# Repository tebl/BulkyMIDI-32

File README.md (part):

# BulkyMIDI-32
When I was young I'd heard rumours about a fantastical sound card for the computer known as the Roland MT-32 - imagining that if it was good enough to be the default sound device for games such as Monkey Island, then it had to be good! Of course I was a kid at the time, the kind that didn't even have enough money to even be allowed inside the kind of stores that would sell this stuff. Fast forward to adulthood and I learned that it wasn't a sound card at all - it was a standalone MIDI-module! The second thing I learned was that they originally were, and still are, incredibly expensive items. Especially for those of us who were born without any sense of rhythm.

Cue other incredibly talented people found on the Internet, in particular for creating the [mt32-pi](https://github.com/dwhinham/mt32-pi) project - allowing people like myself to build a device capable of at least emulating one of these fantastical devices. All it takes is a somewhat cheap, mostly available Raspberry Pi 3 or 4. As with everything I enjoy playing around with, as long as it is simple enough for me to do so - I'll look into building my own version of it. Granted, I may have cheated more than a little bit by starting out with a copy of the design files for [clymsyMIDI](https://github.com/gmcn42/clumsyMIDI) as my starting point.

I had a lot of fun building the original *BulkyMIDI-32*, my process can best be described as an exciting journey down a rabbit hole of all things MIDI including similarly themed audio projects. This resulted in a multitude of adapters built for connecting things together, including a whole host of interesting modules that can be either used with the *BulkyMIDI-32* - or - in many cases they can be also be used by themselves or alongside other vintage music equipment. In order to keep things separate I've split the modules-section so that you'd quickly be able to determine which PCB designs could belong together.

- [1> Modules](#1-modules)
  - [1.1> BulkyMIDI-32](#11-bulkymidi-32)
  - [1.2> BulkyMIDI-32 Audio Switch](#12-bulkymidi-32-audio-switch)
  - [1.3> BulkyMIDI-32 Channel Monitor](#13-bulkymidi-32-channel-monitor)
  - [1.4> BulkyMIDI-32 Channel Monitor 2](#14-bulkymidi-32-channel-monitor-2)
  - [1.5> BulkyMIDI-32 Dexed](#15-bulkymidi-32-dexed)
  - [1.6> BulkyMIDI-32 ExModule](#16-bulkymidi-32-exmodule)
  - [1.7> BulkyMIDI-32 Input Switch](#17-bulkymidi-32-input-switch)
  - [1.8> BulkyMIDI-32 Internal](#18-bulkymidi-32-internal)
  - [1.9> BulkyMIDI-32 Play](#19-bulkymidi-32-play)
  - [1.10> BulkyMIDI-32 Power Switch](#110-bulkymidi-32-power-switch)
  - [1.11> BulkyMIDI-32 VU SIDi](#111-bulkymidi-32-vu-sidi)
- [2> Adapters](#2-adapters)
- [3> Documentation](#3-documentation)
- [4> Acknowledgements](#4-acknowledgements)

# 1> Modules
For the technical details as well as information regarding the modules included by this specific github project, consult the table below. Follow the [documentation](https://github.com/tebl/BulkyMIDI-32/tree/main/documentation) links for build instructions, BOM and anything else you'd need for that specific module. Faceplates and any backplates listed are for the most most part only decorative, allowing you to put together something similar to a case without actually requiring a 3d-printer. Also, check out the [schematics](https://github.com/tebl/BulkyMIDI-32/tree/main/documentation) for more information about the electronic side of things.

As previously mentioned several modules has been designed as part of the same project, these add different functionality and due to their identical form factor - they can all be stacked to build your very own MIDI-mountain! Though they bear the *BulkyMIDI-32* name, they can all be used independently of the main [BulkyMIDI-32](#11-bulkymidi-32)-module - they will communicate using standard MIDI. Should you want to, they should be able to live happily alongside your vintage MIDI-devices.

| Module                            | Description                                      |
| --------------------------------- | ------------------------------------------------ | 
| [BulkyMIDI-32](#11-bulkymidi-32)  | Main *BulkyMIDI-32*-module (running *mt32-pi*).
| [BulkyMIDI-32 Audio Switch](#12-bulkymidi-32-audio-switch) | Module for switching between various audio sources, similar to the source selection switch on a stereo system.
| [BulkyMIDI-32 Channel Monitor](#13-bulkymidi-32-channel-monitor) | MIDI-channel activity monitor, lights up an LED corresponding to the channel on activity. Implemented using basic CMOS logic chips.
| [BulkyMIDI-32 Channel Monitor 2](#14-bulkymidi-32-channel-monitor-2) | Mainly the same as above, except that the hardware is implemented using an *Arduino Pro Micro* and is therefore a lot easier to obtain the parts for.
| [BulkyMIDI-32 Dexed](#15-bulkymidi-32-dexed) | A variant of *BulkyMIDI-32* that was intended for running [MiniDexed](https://github.com/probonopd/MiniDexed).
| [BulkyMIDI-32 ExModule](#16-bulkymidi-32-exmodule) | *BulkyMIDI-32*-styled module for connecting modern WaveTable-modules up to MIDI-devices.
| [BulkyMIDI-32 Input Switch](#16-bulkymidi-32-input-switch) | Module for switching between up to four MIDI sources, the selected input is then replicated to three different THRU-ports. This allows you to easily switch between equipment as well as chain together different systems.
| [BulkyMIDI-32 Internal](#18-bulkymidi-32-internal) | *BulkyMIDI-32* built for installing in a 3.5" PC drivebay.
| [BulkyMIDI-32 Play](#19-bulkymidi-32-play) | Used for playing MIDI-files (*.MID*) from an SD-card using an *Arduino Pro Micro*. The hardware can also be uses as a basis for building a custom MIDI-merger, MIDI-message filtering or simply as a *USB to MIDI*-adapter.
| [BulkyMIDI-32 Power Switch](#110-bulkymidi-32-power-switch) | *BulkyMIDI-32*-module for managing power to other *BulkyMIDI-32*-modules.
| [BulkyMIDI-32 VU SIDi](#111-bulkymidi-32-vu-sidi) | At the moment this is an LM3915-based VU-meter.

## 1.1> BulkyMIDI-32

**Status:** Completed

This is the main attraction of this entire repository. If you came here looking to build an awesome looking mt32-pi, then this is at least one of them. You're given the option of picking the cheaper route by only building up a basic module, that's the main PCB and nothing else. Alternatively, and this is the part that makes it awesome, you can build the whole thing as shown above. Given the really low cost of PCB fabrication on this side of the widely advertised oncoming apocalypse, I recommend that you build a complete unit. The list below will include alternate versions of some boards, so you need to decide which of them you want or need based on their description.

| Module                 | Required    | Description                        | Documentation                      | Order      |
| ---------------------- | ----------- | ---------------------------------- | ---------------------------------- | ---------- |
| [BulkyMIDI-32](https://github.com/tebl/BulkyMIDI-32/tree/main/BulkyMIDI-32%20Module) | Yes | Main module | [Documentation](https://github.com/tebl/BulkyMIDI-32/tree/main/BulkyMIDI-32%20Module), [BOM](https://github.com/tebl/BulkyMIDI-32/blob/main/BulkyMIDI-32%20Module/README.md#3-bom), [Setting it up](https://github.com/tebl/BulkyMIDI-32/blob/main/documentation/setting_it_up.md), [Getting started](https://github.com/tebl/BulkyMIDI-32/blob/main/documentation/getting_started.md) | [PCBWay](https://www.pcbway.com/project/shareproject/BulkyMIDI_32_35d2ed18.html)
| [BulkyMIDI-32 Panel](https://github.com/tebl/BulkyMIDI-32/tree/main/BulkyMIDI-32%20Module%20Panel) | Recommended | Adds a vertical surface for mounting switches and rotary encoder. | [Documentation](https://github.com/tebl/BulkyMIDI-32/tree/main/BulkyMIDI-32%20Module%20Panel), [BOM](https://github.com/tebl/BulkyMIDI-32/tree/main/BulkyMIDI-32%20Module%20Panel/README.md#3-bom) | [PCBWay](https://www.pcbway.com/project/shareproject/BulkyMIDI_32_Module_Panel_17b7fa7c.html)
| [BulkyMIDI-32 Front panel (FP1)](https://github.com/tebl/BulkyMIDI-32/tree/main/faceplates/BulkyMIDI-32%20Module%20FP1) | Optional | Decorative front panel, mounts on [BulkyMIDI-32 Panel](https://github.com/tebl/BulkyMIDI-32/tree/main/BulkyMIDI-32%20Module%20Panel). Designed for use with [BulkyMIDI-32 Extras](https://github.com/tebl/BulkyMIDI-32/tree/main/BulkyMIDI-32%20Extras). | [Documentation](https://github.com/tebl/BulkyMIDI-32/tree/main/faceplates/BulkyMIDI-32%20Module%20FP1) | [PCBWay](https://www.pcbway.com/project/shareproject/BulkyMIDI_32_Module_Faceplate_FP1_92a2878f.html)
| [BulkyMIDI-32 Front panel (FP2)](https://github.com/tebl/BulkyMIDI-32/tree/main/faceplates/BulkyMIDI-32%20Module%20FP2) | Recommended | Decorative front panel, mounts on [BulkyMIDI-32 Panel](https://github.com/tebl/BulkyMIDI-32/tree/main/BulkyMIDI-32%20Module%20Panel) | [Documentation](https://github.com/tebl/BulkyMIDI-32/tree/main/faceplates/BulkyMIDI-32%20Module%20FP2) | [PCBWay](https://www.pcbway.com/project/shareproject/BulkyMIDI_32_Module_Faceplate_FP2_946cc4c8.html)
| [BulkyMIDI-32 Extras](https://github.com/tebl/BulkyMIDI-32/tree/main/BulkyMIDI-32%20Extras) | Optional | Adds passive audio mixing, RS-232 connectivity and RS-232 baud rate translation. | [Documentation](https://github.com/tebl/BulkyMIDI-32/tree/main/BulkyMIDI-32%20Extras), [BOM](https://github.com/tebl/BulkyMIDI-32/tree/main/BulkyMIDI-32%20Extras/README.md#3-bom) | [PCBWay](https://www.pcbway.com/project/shareproject/BulkyMIDI_32_Extras_9be44f98.html)
| [BulkyMIDI-32 Faceplate (FB2)](https://github.com/tebl/BulkyMIDI-32/tree/main/faceplates/BulkyMIDI-32%20FB2) | Optional | Faceplate that goes on top of the device | [Documentation](https://github.com/tebl/BulkyMIDI-32/tree/main/faceplates/BulkyMIDI-32%20FB2) | [PCBWay](https://www.pcbway.com/project/shareproject/BulkyMIDI_32_Faceplate_FB2_c07272e8.html)

## 1.2> BulkyMIDI-32 Audio Switch

**Status:** Completed

One of the drawbacks to using a vintage boombox as my main stereo speaker system in my workshop, is that only has a single audio input - meaning that I would normally have to switch around cables all the time. Ordinarily I shouldn't complain as much about that, as not everyone is lucky enough to have an input - at all! This doesn't solve the problem of not having any, but you do get the option of turning a single input into as many as you'd like with this Audio Switch. If you need more than six, build more than one!

To select the one you want, just push a button and almost instantly you'll hear an exciting click from the corresponding relay. Did I need a relay for this? Probably not. I just like using relays from time to time.

| Module                 | Required    | Description                        | Documentation                      | Order      |
| ---------------------- | ----------- | ---------------------------------- | ---------------------------------- | ---------- |
| [Audio Switch](https://github.com/tebl/BulkyMIDI-32/tree/main/BulkyMIDI-32%20Audio%20Switch) | Yes | Main module | [Documentation](https://github.com/tebl/BulkyMIDI-32/tree/main/BulkyMIDI-32%20Audio%20Switch), [BOM](https://github.com/tebl/BulkyMIDI-32/blob/main/BulkyMIDI-32%20Audio%20Switch/README.md#3-bom) | [PCBWay](https://www.pcbway.com/project/shareproject/BulkyMIDI_32_Audio_Switch_118316c8.html)
| [Audio Switch Panel](https://github.com/tebl/BulkyMIDI-32/tree/main/BulkyMIDI-32%20Audio%20Switch%20Panel) | Optional | Adds a vertical surface installing switches as well as adding channel indicator LEDs. | [Documentation](https://github.com/tebl/BulkyMIDI-32/tree/main/BulkyMIDI-32%20Audio%20Switch%20Panel), [BOM](https://github.com/tebl/BulkyMIDI-32/blob/main/BulkyMIDI-32%20Audio%20Switch%20Panel/README.md#3-bom) | [PCBWay](https://www.pcbway.com/project/shareproject/BulkyMIDI_32_Audio_Switch_Panel_a10b5ecb.html)
| [Audio Switch Front Panel (FP1)](https://github.com/tebl/BulkyMIDI-32/tree/main/faceplates/BulkyMIDI-32%20Audio%20Switch%20FP1) | Optional | Decorative front panel, mounts on [Audio Switch Panel](https://github.com/tebl/BulkyMIDI-32/tree/main/BulkyMIDI-32%20Audio%20Switch%20Panel). | [Documentation](https://github.com/tebl/BulkyMIDI-32/tree/main/faceplates/BulkyMIDI-32%20Audio%20Switch%20FP1) | [PCBWay](https://www.pcbway.com/project/shareproject/BulkyMIDI_32_Audio_Switch_Faceplate_FP1_fc2b542a.html)
| [BulkyMIDI-32 Faceplate (FB2)](https://github.com/tebl/BulkyMIDI-32/tree/main/faceplates/BulkyMIDI-32%20FB2) | Optional | Faceplate that goes on top of the device | [Documentation](https://github.com/tebl/BulkyMIDI-32/tree/main/faceplates/BulkyMIDI-32%20FB2) | [PCBWay](https://www.pcbway.com/project/shareproject/BulkyMIDI_32_Faceplate_FB2_c07272e8.html)

## 1.3> BulkyMIDI-32 Channel Monitor

**Status:** Working, but documentation is missing.

One of the first things I wanted to add to the *BulkyMIDI-32* was more blinking lights, as it turns out there were devices back in the day that did this - the were called channel monitors. Their purpose is simply to have an LED for each of the 16 MIDI channels, then as a MIDI-message passes through that contains channel information - the corresponding LED is lit up and will stay on for some time.

The circuit design was based on an article by W. Dunczewski, titled *MIDI Channel Monitor* and was printed in the 1993 october issue of Elektor Electronics. Besides the obvious attraction to blinking lights in controlled forms, what I liked about it is that everything is implemented entirely in basic CMOS logic chips (there's no traditional CPU or MCU handling the data).

| Module                 | Required    | Description                        | Documentation                      | Order      |
| ---------------------- | ----------- | ---------------------------------- | ---------------------------------- | ---------- |
| [Channel Monitor](https://github.com/tebl/BulkyMIDI-32/tree/main/BulkyMIDI-32%20Channel) | Yes | Main module | [Documentation](https://github.com/tebl/BulkyMIDI-32/tree/main/BulkyMIDI-32%20Channel), [BOM](https://github.com/tebl/BulkyMIDI-32/blob/main/BulkyMIDI-32%20Channel/README.md#3-bom) | PCBWay
| [Channel Monitor Panel](https://github.com/tebl/BulkyMIDI-32/tree/main/BulkyMIDI-32%20Channel%20Panel) | Optional | Adds a vertical surface for mounting the 16 channel LEDs. | [Documentation](https://github.com/tebl/BulkyMIDI-32/tree/main/BulkyMIDI-32%20Channel%20Panel), [BOM](https://github.com/tebl/BulkyMIDI-32/blob/main/BulkyMIDI-32%20Channel20Panel/README.md#3-bom) | PCBWay
| [Channel Monitor Front Panel (FP1)](https://github.com/tebl/BulkyMIDI-32/tree/main/faceplates/BulkyMIDI-32%20Channel%20FP1) | Optional | Decorative front panel, mounts on [Channel Monitor Panel](https://github.com/tebl/BulkyMIDI-32/tree/main/BulkyMIDI-32%20Channel%20Panel). | [Documentation](https://github.com/tebl/BulkyMIDI-32/tree/main/faceplates/BulkyMIDI-32%20Channel%20FP1) | PCBWay
| [BulkyMIDI-32 Faceplate (FB2)](https://github.com/tebl/BulkyMIDI-32/tree/main/faceplates/BulkyMIDI-32%20FB2) | Optional | Faceplate that goes on top of the device | [Documentation](https://github.com/tebl/BulkyMIDI-32/tree/main/faceplates/BulkyMIDI-32%20FB2) | [PCBWay](https://www.pcbway.com/project/shareproject/BulkyMIDI_32_Faceplate_FB2_c07272e8.html)

## 1.4> BulkyMIDI-32 Channel Monitor 2

**Status:** Working, but documentation is missing.

This module displays MIDI-channel activity in realtime, with an LED for each of the 16 channels. While it effectively does the same as the [BulkyMIDI-32 Channel Monitor](#13-bulkymidi-32-channel-monitor), I also wanted to build a version that could be put together using parts that aren't quite as *vintage* as the parts required by that module.

In the end, the core of the module was implemented using an Arduino Pro Micro in combination with a couple of shift registers. In theory the board can be built up as a simple *USB-to-MIDI* converter, or it can be used to have the MCU process MIDI-messages - note that Arduino *sketches* to do any of this do not exist. 

| Module                 | Required    | Description                        | Documentation                      | Order      |
| ---------------------- | ----------- | ---------------------------------- | ---------------------------------- | ---------- |
| [Channel Monitor 2](https://github.com/tebl/BulkyMIDI-32/tree/main/BulkyMIDI-32%20Channel%202) | Yes | Main module | [Documentation](https://github.com/tebl/BulkyMIDI-32/tree/main/BulkyMIDI-32%20Channel%202), [BOM](https://github.com/tebl/BulkyMIDI-32/blob/main/BulkyMIDI-32%20Channel%202/README.md#3-bom) | PCBWay
| [Channel Monitor Panel](https://github.com/tebl/BulkyMIDI-32/tree/main/BulkyMIDI-32%20Channel%20Panel) | Optional | Adds a vertical surface for mounting the 16 channel LEDs. | [Documentation](https://github.com/tebl/BulkyMIDI-32/tree/main/BulkyMIDI-32%20Channel%20Panel), [BOM](https://github.com/tebl/BulkyMIDI-32/blob/main/BulkyMIDI-32%20Channel20Panel/README.md#3-bom) | PCBWay
| [Channel Monitor Front Panel (FP1)](https://github.com/tebl/BulkyMIDI-32/tree/main/faceplates/BulkyMIDI-32%20Channel%20FP1) | Optional | Decorative front panel, mounts on [Channel Monitor Panel](https://github.com/tebl/BulkyMIDI-32/tree/main/BulkyMIDI-32%20Channel%20Panel). | [Documentation](https://github.com/tebl/BulkyMIDI-32/tree/main/faceplates/BulkyMIDI-32%20Channel%20FP1) | PCBWay
| [BulkyMIDI-32 Faceplate (FB2)](https://github.com/tebl/BulkyMIDI-32/tree/main/faceplates/BulkyMIDI-32%20FB2) | Optional | Faceplate that goes on top of the device | [Documentation](https://github.com/tebl/BulkyMIDI-32/tree/main/faceplates/BulkyMIDI-32%20FB2) | [PCBWay](https://www.pcbway.com/project/shareproject/BulkyMIDI_32_Faceplate_FB2_c07272e8.html)

## 1.5> BulkyMIDI-32 Dexed

**Status:** Untested prototype

A variant of *BulkyMIDI-32* that was intended for running [MiniDexed](https://github.com/probonopd/MiniDexed), a software that is similar to *MT32-PI* - except that it instead emulates up to eight Yamaha DX7 synthesizers on mostly the same hardware. I built one up and played around with it, my conclusion afterwards is that while it *may* work - I have absolutely no idea of how to use it. Or even a real keyboard for that matter. So in case someone finds it interesting enough to build one up using the files provided, please tell me whether it actually works. 

## 1.6> BulkyMIDI-32 ExModule

**Status:** Completed

There was a time when PC soundcards, mostly ISA, came with a *WaveTable*-header for attaching *WaveTable*-modules directly onto it it. Originally devised for mounting a separate *WaveBlaster*-module onto a *Creative Soundblaster 16*, but most often they're just referred to as *WaveTable*-headers as the form factor was inevitably adopted by several other companies who made similar modules with their own chipsets on it.

Ordering a selection of more modern modules from [serdashop.com](https://www.serdashop.com/) for installing into one of my vintage PCs, I couldn't decide on which one to put where - until I finally decided and realized that my AWE32 doesn't even have that feature. So for a year or so they've lived in the box the came in, buy in the end I figured it was time to do something with them. So I started building something to use them externally instead - following the guide up on [atari.joska.no](https://atari.joska.no/db50xg/), itself referencing an article printed in Elektor Electronics (july/august 1997), I ended up with the *BulkyMIDI-32 ExModule*. Plug a MIDI-cable into it, hook the audio output up to your amplifier and enjoy!

| Module                 | Required    | Description                        | Documentation                      | Order      |
| ---------------------- | ----------- | ---------------------------------- | ---------------------------------- | ---------- |
| [ExModule](https://github.com/tebl/BulkyMIDI-32/tree/main/BulkyMIDI-32%20ExModule) | Yes | Main module | [Documentation](https://github.com/tebl/BulkyMIDI-32/tree/main/BulkyMIDI-32%20ExModule), [BOM](https://github.com/tebl/BulkyMIDI-32/blob/main/BulkyMIDI-32%20ExModule/README.md#3-bom) | [PCBWay](https://www.pcbway.com/project/shareproject/BulkyMIDI_32_ExModule_6564c365.html)
| [ExModule Panel](https://github.com/tebl/BulkyMIDI-32/tree/main/BulkyMIDI-32%20ExModule%20Panel) | Optional | Adds a vertical surface installing switches as well as adding channel indicator LEDs. | [Documentation](https://github.com/tebl/BulkyMIDI-32/tree/main/BulkyMIDI-32%20ExModule%20Panel), [BOM](https://github.com/tebl/BulkyMIDI-32/blob/main/BulkyMIDI-32%20ExModule%20Panel/README.md#3-bom) | [PCBWay](https://www.pcbway.com/project/shareproject/BulkyMIDI_32_ExModule_Panel_8050038f.html)
| [ExModule Front Panel (FP1)](https://github.com/tebl/BulkyMIDI-32/tree/main/faceplates/BulkyMIDI-32%20ExModule%20FP1) | Optional | Decorative front panel, mounts on [ExModule Panel](https://github.com/tebl/BulkyMIDI-32/tree/main/BulkyMIDI-32%20ExModule%20Panel). | [Documentation](https://github.com/tebl/BulkyMIDI-32/tree/main/faceplates/BulkyMIDI-32%20ExModule%20FP1) | [PCBWay](https://www.pcbway.com/project/shareproject/BulkyMIDI_32_ExModule_Faceplate_FP1_640ef0bc.html)
| [BulkyMIDI-32 Faceplate (FB2)](https://github.com/tebl/BulkyMIDI-32/tree/main/faceplates/BulkyMIDI-32%20FB2) | Optional | Faceplate that goes on top of the device | [Documentation](https://github.com/tebl/BulkyMIDI-32/tree/main/faceplates/BulkyMIDI-32%20FB2) | [PCBWay](https://www.pcbway.com/project/shareproject/BulkyMIDI_32_Faceplate_FB2_c07272e8.html)

## 1.7> BulkyMIDI-32 Input Switch

**Status:** Completed

This module was created in order to easily switch between different MIDI inputs, the selected input is then replicated to three different THRU-ports. What this allows me to do on the input-side is to select between a keyboard, a USB MIDI-interfaces connected to a modern system and that of a  vintage computer system. Duplicating the MIDI-messages on different THRU-ports allow me to send the same data to several MIDI-devices, such as an original *Roland MT-32* as well as a *MT32-PI* (such as the BulkyMIDI-32 itself). 

| Module                 | Required    | Description                        | Documentation                      | Order      |
| ---------------------- | ----------- | ---------------------------------- | ---------------------------------- | ---------- |
| [Input Switch](https://github.com/tebl/BulkyMIDI-32/tree/main/BulkyMIDI-32%20Input%20Switch) | Yes | Main module | [Documentation](https://github.com/tebl/BulkyMIDI-32/tree/main/BulkyMIDI-32%20Audio%20Switch), [BOM](https://github.com/tebl/BulkyMIDI-32/blob/main/BulkyMIDI-32%20Audio%20Switch/README.md#3-bom) | PCBWay
| [Input Switch Panel](https://github.com/tebl/BulkyMIDI-32/tree/main/BulkyMIDI-32%20Input%20Switch%20Panel) | Optional | Adds a vertical surface installing switches as well as adding indicator LEDs. | [Documentation](https://github.com/tebl/BulkyMIDI-32/tree/main/BulkyMIDI-32%20Input%20Switch%20Panel), [BOM](https://github.com/tebl/BulkyMIDI-32/blob/main/BulkyMIDI-32%20Input%20Switch%20Panel/README.md#3-bom) | PCBWay
| [Input Switch Front Panel (FP1)](https://github.com/tebl/BulkyMIDI-32/tree/main/faceplates/BulkyMIDI-32%20Input%20Switch%20FP1) | Optional | Decorative front panel, mounts on [Input Switch Panel](https://github.com/tebl/BulkyMIDI-32/tree/main/BulkyMIDI-32%20Input%20Switch%20Panel). | [Documentation](https://github.com/tebl/BulkyMIDI-32/tree/main/faceplates/BulkyMIDI-32%20Input%20Switch%20FP1) | PCBWay
| [Input Switch Faceplate (FB2)](https://github.com/tebl/BulkyMIDI-32/tree/main/faceplates/BulkyMIDI-32%20Input%20Switch%20FB2) | Optional | Faceplate that goes on top of the device, similar to the two below - except it's missing a hole. | [Documentation](https://github.com/tebl/BulkyMIDI-32/tree/main/faceplates/BulkyMIDI-32%20Input%20Switch%20FB2) | PCBWay
| [BulkyMIDI-32 Faceplate (FB2)](https://github.com/tebl/BulkyMIDI-32/tree/main/faceplates/BulkyMIDI-32%20FB2) | Optional | Faceplate that goes on top of the device | [Documentation](https://github.com/tebl/BulkyMIDI-32/tree/main/faceplates/BulkyMIDI-32%20FB2) | [PCBWay](https://www.pcbway.com/project/shareproject/BulkyMIDI_32_Faceplate_FB2_c07272e8.html)

## 1.8> BulkyMIDI-32 Internal

**Status:** Working prototype

In many ways this is the module that this whole thing has been building towards, a 3.5" drive bay expansion for vintage PCs. Might fit into more equipment than this, but mainly just the blocky beige thing that you remember from your childhood (usually next to a CRT). Is this a sane thing to build without any kind of working 3d-printer available? No, it probably isn't. Did I build it anyway? Yes, and you're looking at the only finished version of it. Is it actually finished? No. Probably needs a bit of tweaking and the documentation to go with it.

## 1.9> BulkyMIDI-32 Play

**Status:** Completed

In many ways the missing module when it comes to playing around with a Roland MT-32, both the vintage kind as well as the emulated version that is the main *BulkyMIDI-32* module (running *mt32-pi*) - simply playing back a *.MID*-file without a computer attached to it. Implemented with an Arduino Pro Micro at its heart, you can put your files on an SD-card and play them back - use a long press when starting playback to loop the file, another long press to stop playback. During playback the rotary encoder encoder can be used to speed up or slow down the tempo.

Given that the designs have provisions for more than the expected number of MIDI-ports, a change in firmware can allow the hardware design to be used for entirely different purposes such as MIDI-message filtering, merging inputs and similar functionality.  

| Module                 | Required    | Description                        | Documentation                      | Order      |
| ---------------------- | ----------- | ---------------------------------- | ---------------------------------- | ---------- |
| [Play](https://github.com/tebl/BulkyMIDI-32/tree/main/BulkyMIDI-32%20Play) | Yes | Main module | [Documentation](https://github.com/tebl/BulkyMIDI-32/tree/main/BulkyMIDI-32%20Play), [BOM](https://github.com/tebl/BulkyMIDI-32/blob/main/BulkyMIDI-32%20Play/README.md#3-bom) | PCBWay
| [Play Panel](https://github.com/tebl/BulkyMIDI-32/tree/main/BulkyMIDI-32%20Play%20Panel) | Optional | Adds a vertical surface for oled-display and rotary encoder. | [Documentation](https://github.com/tebl/BulkyMIDI-32/tree/main/BulkyMIDI-32%20Play%20Panel), [BOM](https://github.com/tebl/BulkyMIDI-32/tree/main/BulkyMIDI-32%20Play%20Panel/README.md#3-bom) | PCBWay
| [Play Front Panel (FP1)](https://github.com/tebl/BulkyMIDI-32/tree/main/faceplates/BulkyMIDI-32%20Play%20FP1) | Optional | Decorative front panel, mounts on [Play Panel](https://github.com/tebl/BulkyMIDI-32/tree/main/BulkyMIDI-32%20Play%20Panel). | [Documentation](https://github.com/tebl/BulkyMIDI-32/tree/main/faceplates/BulkyMIDI-32%20Play%20FP1) | PCBWay
| [BulkyMIDI-32 Faceplate (FB2)](https://github.com/tebl/BulkyMIDI-32/tree/main/faceplates/BulkyMIDI-32%20FB2) | Optional | Faceplate that goes on top of the device | [Documentation](https://github.com/tebl/BulkyMIDI-32/tree/main/faceplates/BulkyMIDI-32%20FB2) | [PCBWay](https://www.pcbway.com/project/shareproject/BulkyMIDI_32_Faceplate_FB2_c07272e8.html)

## 1.10> BulkyMIDI-32 Power Switch
**Status:** Working, but last revision has not been tested.

Looking at this repository and the various devices contained within it, you'll soon get the impression that no man could possibly own that many 5v power supplies with that exact barrel plug already on it (2.1mm x 5.5mm barrel connector). I don't. I own exactly two, so that's one for the main BulkyMIDI-32 and one for everything else. So I got the idea that I would make something like the Audio Switch or Input Switch, except with power! And because I wanted a push to turn on, but really wanted a hold to turn off - I added an Arduino to the board. And some more relays. Because relays are cool, and a lot easier to understand for someone like me. You feed it power, then the other power connectors are hooked up to your other devices. In order to do so, you use a cable with a male plug on both ends (AliExpress has them listed as *DC male to male CCTV adapter connector cords*).

The design has provisions for using the first channel as a source for power, possibly with a different polarity. This is done by opting not to install the corresponding relay for the first channel, and changing out some of the wire links. Only reason I'm mentioning it in the first place is that music equipment traditionally use the same type of plug, but at a completely different voltage and polarity from what all of my *BulkyMIDI-32*-modules work with. If you mess up your cabling at some point, then there should be expectations of of smoke and tears, but it's nice to know that it's there as an option. If you know what you're doing.

## 1.11> BulkyMIDI-32 VU SIDi

**Status:** Prototype, with issues to work out

This is a module that I'll probably have to rethink properly, mostly because of attempting to integrate a little too much in one go without a proper understanding of either of them. The first part of it is a VU-meter based on the LM3915 chip which isn't a solution I particularly enjoyed using, at least in part due to one of the two modes supported by the chip doesn't really work properly when powered from 5v. The other mode is too flickery for my comfort.

The *SIDi*-part of it was based directly on github-project [SIDI](https://github.com/doctea/SIDI) by user *doctea*, and I can't figure out how to get it to work. This probably isn't a problem with the code, but more my lack of understanding how to work with a music chip directly. I'm not a musician or even know how to play any sort of instrument, so it is a case of biting off more than I can chew - at least for the forseeable future.

# 2> Adapters
Separate from the main modules are several adapters, designed for use with the *BulkyMIDI-32* in particular though most of them simply speak standard MIDI - so they should work with original equipment such as the original *Roland MT-32*. Follow the included in the table below for details such as build instructions, BOM and anything else you'd need for that specific module. The repository also includes a folder for [schematics](https://github.com/tebl/BulkyMIDI-32/tree/main/documentation/schematic/adapters) in PDF-format, these will be needed in order to track down any faults you encounter when building up and testing the adapters.

| Module                 | Required    | Description                        | Documentation                      | Order      |
| ---------------------- | ----------- | ---------------------------------- | ---------------------------------- | ---------- |
| [Amiga MIDI Interface (DB25)](https://github.com/tebl/BulkyMIDI-32/tree/main/adapters/BulkyMIDI-32%20Amiga) | Optional | RS-232 to MIDI adapter for Amiga 500/600/1200/2000/3000/4000. | [Documentation](https://github.com/tebl/BulkyMIDI-32/tree/main/adapters/BulkyMIDI-32%20Amiga), [BOM](https://github.com/tebl/BulkyMIDI-32/tree/main/adapters/BulkyMIDI-32%20Amiga#3-bom) | [PCBWay](https://www.pcbway.com/project/shareproject/Amiga_MIDI_Interface_DB25_ee22ba2d.html)
| [Amiga MIDI Interface (IDC)](https://github.com/tebl/BulkyMIDI-32/tree/main/adapters/BulkyMIDI-32%20Amiga%20IDC) | Optional | RS-232 to MIDI adapter for Amiga 500/600/1200/2000/3000/4000. Use with IDC to DB25 cable. | [Documentation](https://github.com/tebl/BulkyMIDI-32/tree/main/adapters/BulkyMIDI-32%20Amiga%20IDC), [BOM](https://github.com/tebl/BulkyMIDI-32/tree/main/adapters/BulkyMIDI-32%20Amiga%20IDC#3-bom) | [PCBWay](https://www.pcbway.com/project/shareproject/Amiga_MIDI_Interface_IDC_81756c6e.html)
| [Evolution Mk-7 Adapter](https://github.com/tebl/BulkyMIDI-32/tree/main/adapters/BulkyMIDI-32%20Mk7%20Adapter) | Optional | The Evolution Mk-7 MIDI keyboard only came with a DB15-connector as its only output, intended for plugging into a soundcard. This adapts that to regular 5-pin DIN-sockets. | [Documentation](https://github.com/tebl/BulkyMIDI-32/tree/main/adapters/BulkyMIDI-32%20Mk7%20Adapter), [BOM](https://github.com/tebl/BulkyMIDI-32/blob/main/adapters/BulkyMIDI-32%20Mk7%20Adapter/README.md#3-bom) | PCBWay
| [Gameport (DB15)](https://github.com/tebl/BulkyMIDI-32/tree/main/adapters/BulkyMIDI-32%20Gameport) | Optional | Adapter for plugging a MIDI-cable directly into the gameport on several common sound cards. | [Documentation](https://github.com/tebl/BulkyMIDI-32/tree/main/adapters/BulkyMIDI-32%20Gameport), [BOM](https://github.com/tebl/BulkyMIDI-32/blob/main/adapters/BulkyMIDI-32%20Gameport/README.md#3-bom) | [PCBWay](https://www.pcbway.com/project/shareproject/Gameport_MIDI_Interface_DB15_832b357e.html)
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
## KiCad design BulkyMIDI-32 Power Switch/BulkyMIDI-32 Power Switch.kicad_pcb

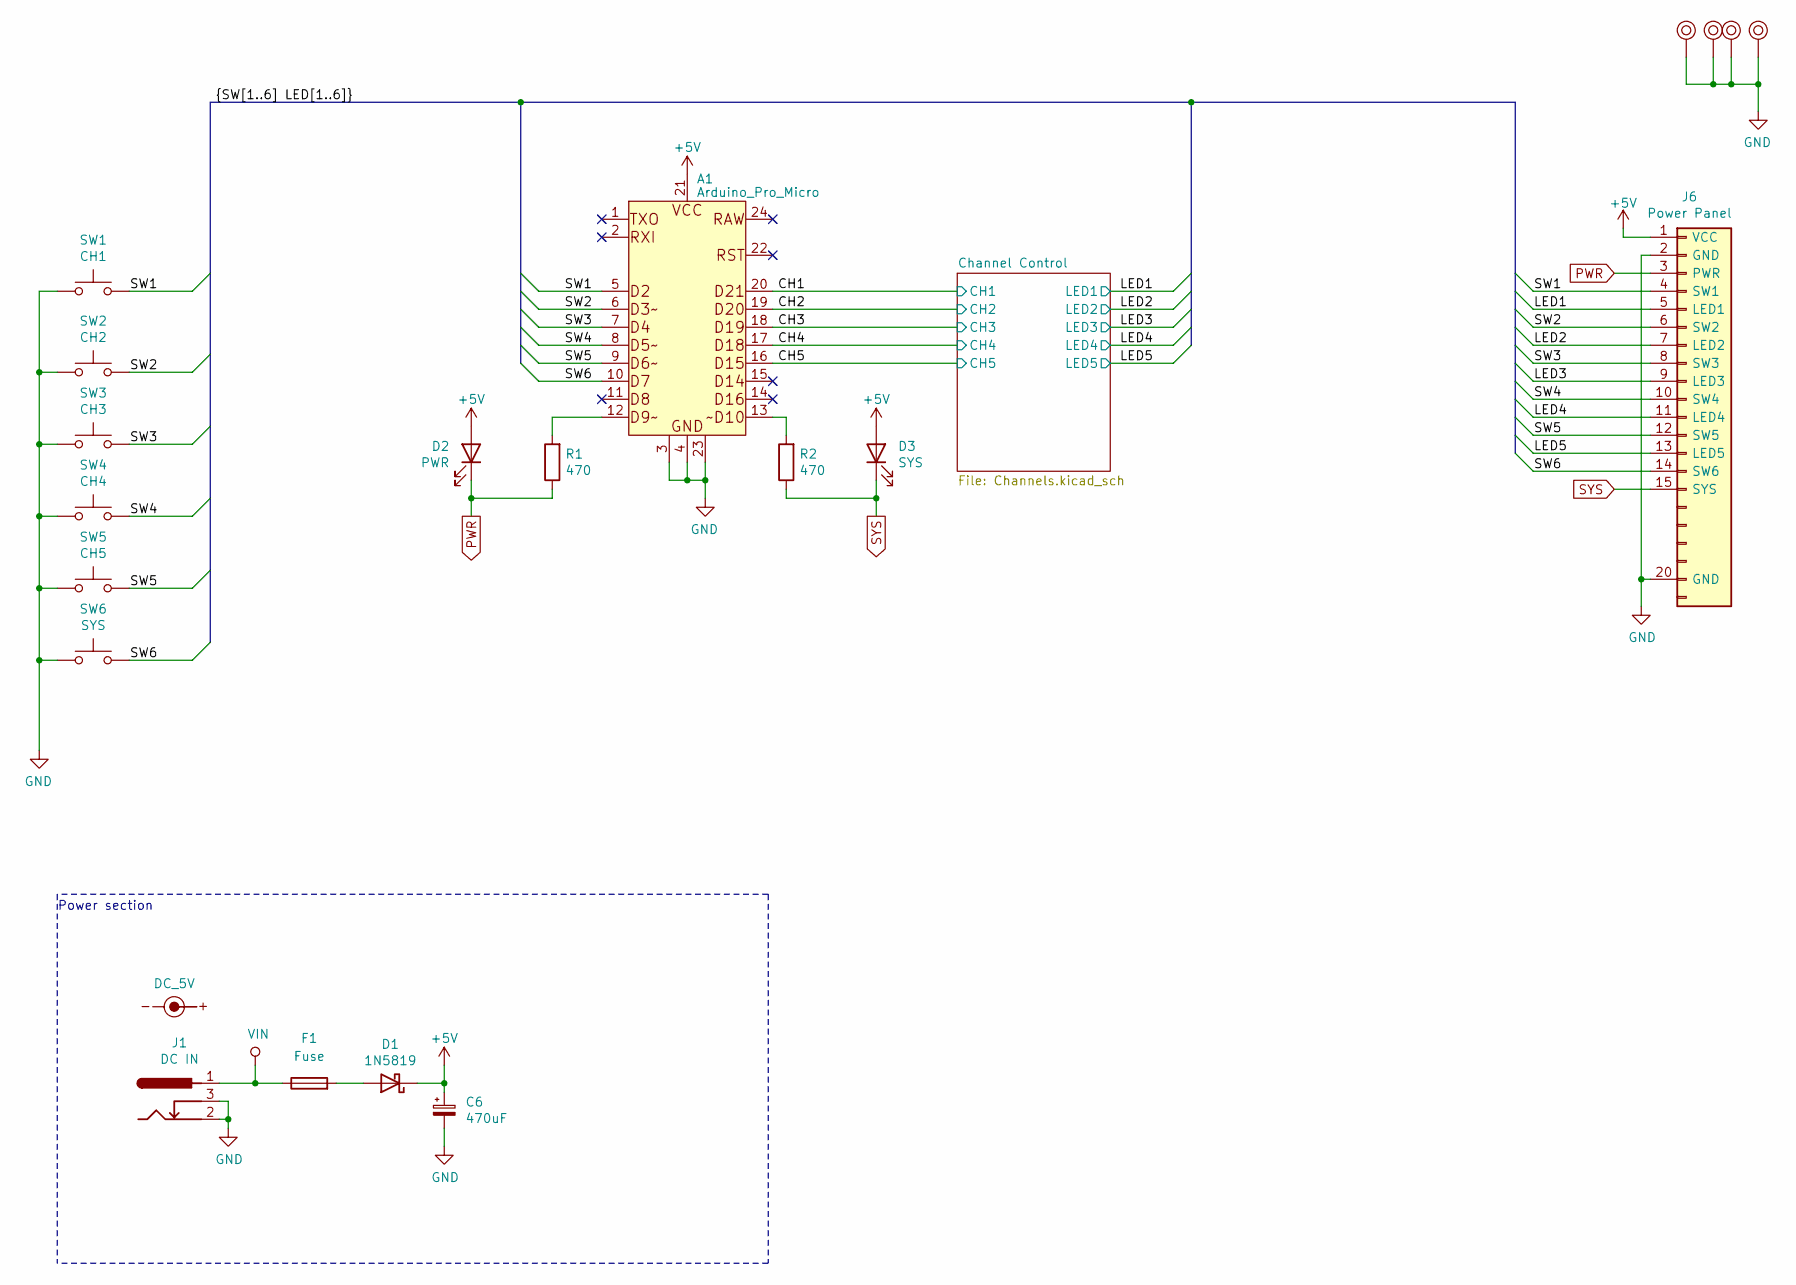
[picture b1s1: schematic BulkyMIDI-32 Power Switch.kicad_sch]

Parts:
A1: Arduino_Pro_Micro
C6: 470uF; CP_Radial_D8.0mm_P3.50mm
D1: 1N5819; D_DO-41_SOD81_P10.16mm_Horizontal
D2: PWR; LED_D3.0mm
D3: SYS; LED_D3.0mm
F1: Fuse; Fuseholder5x20_horiz_SemiClosed_Casing10x25mm
J1: DC IN; BARREL_JACK
J6: Power Panel; Power_Panel
M1, M2, M3, M4: Mounting; M3_pin
R1, R2: 470; R_Axial_DIN0207_L6.3mm_D2.5mm_P10.16mm_Horizontal
SW1: CH1; SW_Tactile_SPST_Angled_PTS645Vx39-2LFS
SW2: CH2; SW_Tactile_SPST_Angled_PTS645Vx39-2LFS
SW3: CH3; SW_Tactile_SPST_Angled_PTS645Vx39-2LFS
SW4: CH4; SW_Tactile_SPST_Angled_PTS645Vx39-2LFS
SW5: CH5; SW_Tactile_SPST_Angled_PTS645Vx39-2LFS
SW6: SYS; SW_Tactile_SPST_Angled_PTS645Vx39-2LFS
SYM1: DC_5V; PWR_Specification

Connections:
+5V: A1.21 (VCC), C6.1, D1.1 (K), D2.2 (A), D3.2 (A), J6.1 (VCC); also elsewhere on the board
/CH1: A1.20 (D21); also elsewhere on the board
/CH2: A1.19 (D20); also elsewhere on the board
/CH3: A1.18 (D19); also elsewhere on the board
/CH4: A1.17 (D18); also elsewhere on the board
/CH5: A1.16 (D15); also elsewhere on the board
/LED1: J6.5 (LED1); also elsewhere on the board
/LED2: J6.7 (LED2); also elsewhere on the board
/LED3: J6.9 (LED3); also elsewhere on the board
/LED4: J6.11 (LED4); also elsewhere on the board
/LED5: J6.13 (LED5); also elsewhere on the board
/SW1: A1.5 (D2), J6.4 (SW1), SW1.1
/SW2: A1.6 (D3), J6.6 (SW2), SW2.1
/SW3: A1.7 (D4), J6.8 (SW3), SW3.1
/SW4: A1.8 (D5), J6.10 (SW4), SW4.1
/SW5: A1.9 (D6), J6.12 (SW5), SW5.1
/SW6: A1.10 (D7), J6.14 (SW6), SW6.1
GND: A1.3 (GND), A1.4 (GND), A1.23 (GND), C6.2, J1.2, J1.3, J6.2 (GND), J6.20 (GND), M1.1, M2.1, M3.1, M4.1, SW1.2, SW2.2, SW3.2, SW4.2, SW5.2, SW6.2; also elsewhere on the board
unnamed: A1.12 (D9), R1.2
unnamed: A1.13 (D10), R2.2
unnamed: D1.2 (A), F1.2
PWR: D2.1 (K), J6.3 (PWR), R1.1
SYS: D3.1 (K), J6.15 (SYS), R2.1
VIN: F1.1, J1.1; also elsewhere on the board

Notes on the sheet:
Power section

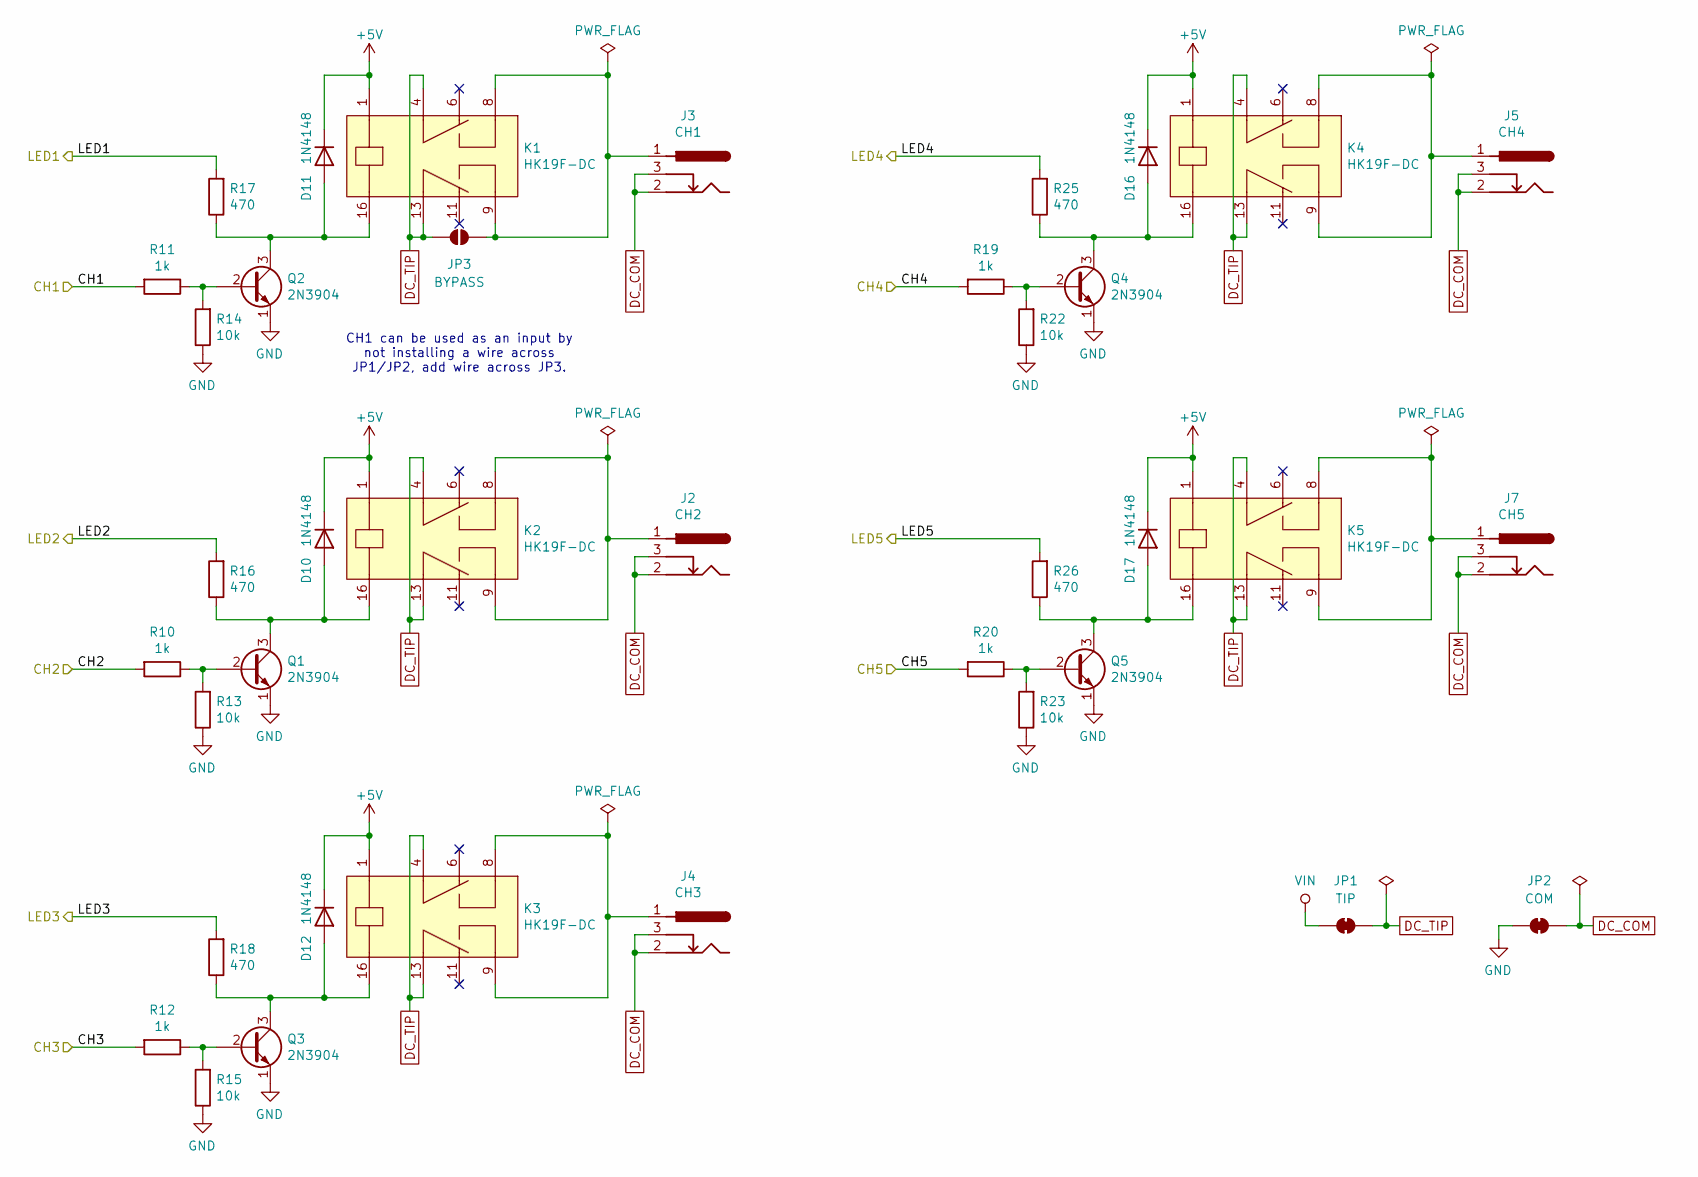
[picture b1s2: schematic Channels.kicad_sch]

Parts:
D10, D11, D12, D16, D17: 1N4148; D_DO-35_SOD27_P7.62mm_Horizontal
J2: CH2; BARREL_JACK
J3: CH1; BARREL_JACK
J4: CH3; BARREL_JACK
J5: CH4; BARREL_JACK
J7: CH5; BARREL_JACK
JP1: TIP; WireLink
JP2: COM; WireLink
JP3: BYPASS; WireLink
K1, K2, K3, K4, K5: HK19F-DC
Q1, Q2, Q3, Q4, Q5: 2N3904; TO-92_Inline_Wide
R10, R11, R12, R19, R20: 1k; R_Axial_DIN0207_L6.3mm_D2.5mm_P10.16mm_Horizontal
R13, R14, R15, R22, R23: 10k; R_Axial_DIN0207_L6.3mm_D2.5mm_P10.16mm_Horizontal
R16, R17, R18, R25, R26: 470; R_Axial_DIN0207_L6.3mm_D2.5mm_P10.16mm_Horizontal

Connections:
+5V: D10.1 (K), D11.1 (K), D12.1 (K), D16.1 (K), D17.1 (K), K1.1, K2.1, K3.1, K4.1, K5.1; also elsewhere on the board
/CH1: R11.2; also elsewhere on the board
/CH2: R10.2; also elsewhere on the board
/CH3: R12.2; also elsewhere on the board
/CH4: R19.2; also elsewhere on the board
/CH5: R20.2; also elsewhere on the board
/LED1: R17.2; also elsewhere on the board
/LED2: R16.2; also elsewhere on the board
/LED3: R18.2; also elsewhere on the board
/LED4: R25.2; also elsewhere on the board
/LED5: R26.2; also elsewhere on the board
DC_COM: J2.2, J2.3, J3.2, J3.3, J4.2, J4.3, J5.2, J5.3, J7.2, J7.3, JP2.2 (B)
DC_TIP: JP1.2 (B), JP3.1 (A), K1.4 (COM_1), K1.13 (COM_2), K2.4 (COM_1), K2.13 (COM_2), K3.4 (COM_1), K3.13 (COM_2), K4.4 (COM_1), K4.13 (COM_2), K5.4 (COM_1), K5.13 (COM_2)
GND: JP2.1 (A), Q1.1 (E), Q2.1 (E), Q3.1 (E), Q4.1 (E), Q5.1 (E), R13.1, R14.1, R15.1, R22.1, R23.1; also elsewhere on the board
unnamed: D10.2 (A), K2.16, Q1.3 (C), R16.1
unnamed: D11.2 (A), K1.16, Q2.3 (C), R17.1
unnamed: D12.2 (A), K3.16, Q3.3 (C), R18.1
unnamed: D16.2 (A), K4.16, Q4.3 (C), R25.1
unnamed: D17.2 (A), K5.16, Q5.3 (C), R26.1
unnamed: J3.1, JP3.2 (B), K1.8 (NO_1), K1.9 (NO_2)
unnamed: J2.1, K2.8 (NO_1), K2.9 (NO_2)
unnamed: J4.1, K3.8 (NO_1), K3.9 (NO_2)
unnamed: J5.1, K4.8 (NO_1), K4.9 (NO_2)
unnamed: J7.1, K5.8 (NO_1), K5.9 (NO_2)
unnamed: Q1.2 (B), R10.1, R13.2
unnamed: Q2.2 (B), R11.1, R14.2
unnamed: Q3.2 (B), R12.1, R15.2
unnamed: Q4.2 (B), R19.1, R22.2
unnamed: Q5.2 (B), R20.1, R23.2
VIN: JP1.1 (A); also elsewhere on the board

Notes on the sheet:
CH1 can be used as an input by not installing a wire across JP1/JP2, add wire across JP3.

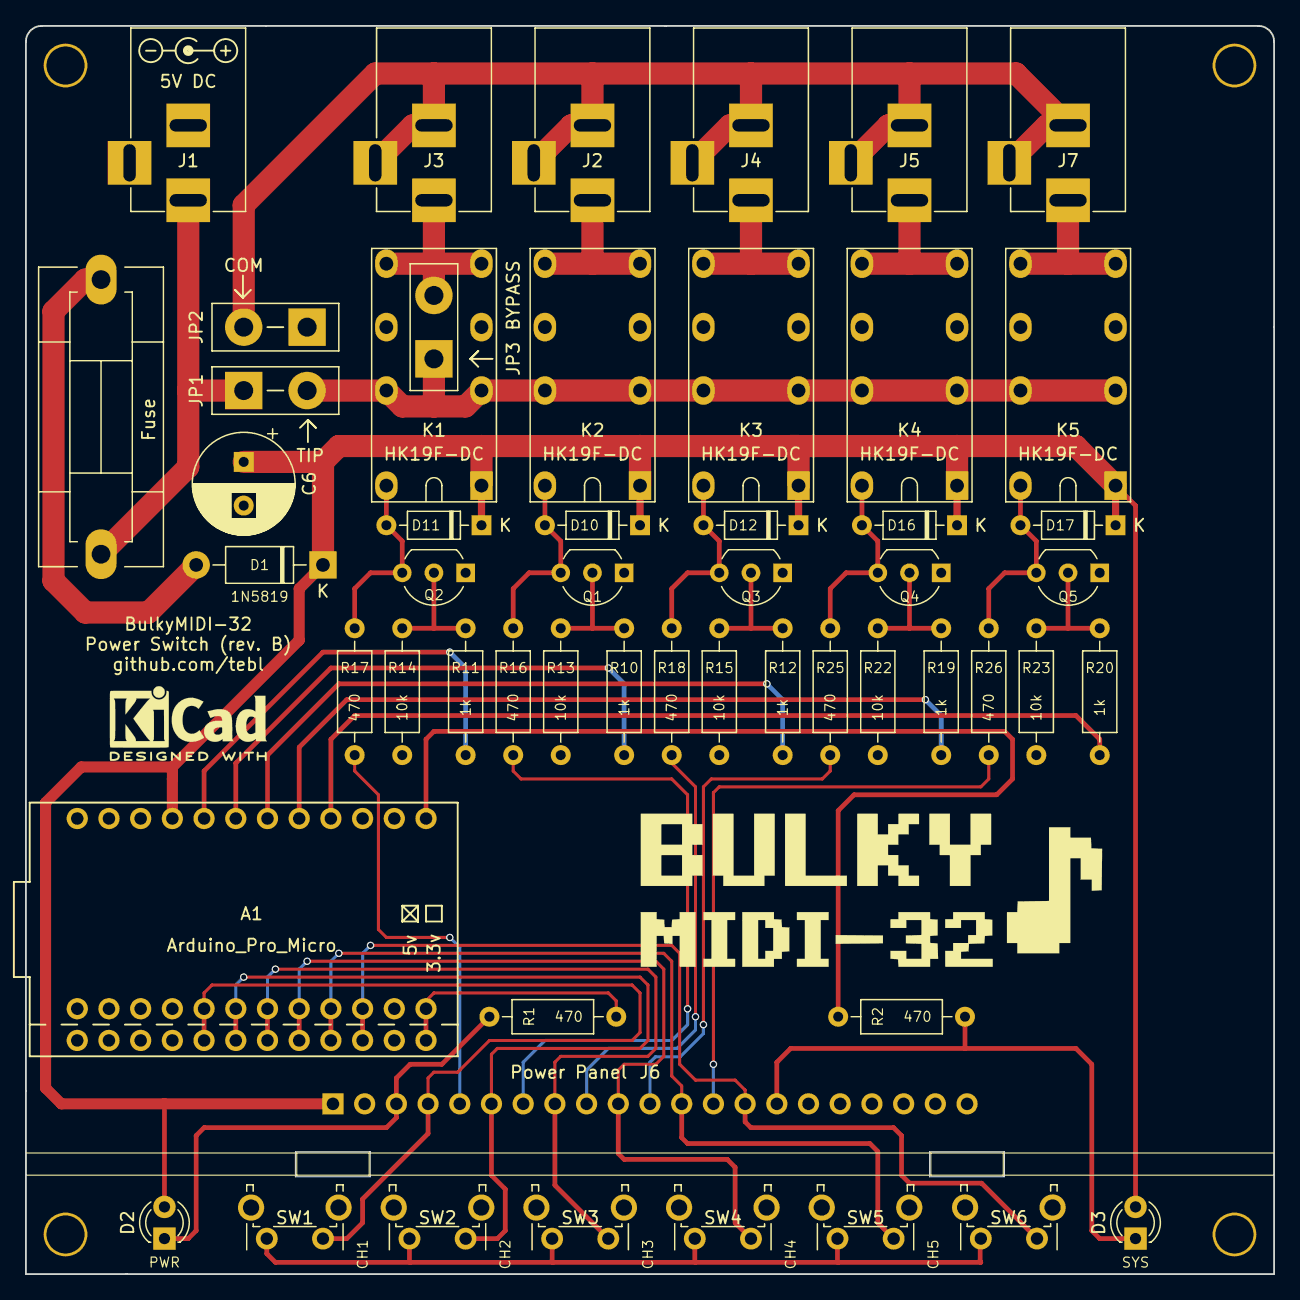
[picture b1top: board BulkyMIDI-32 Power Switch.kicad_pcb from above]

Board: 2 copper layers, 100.0 x 100.0 mm, 59 parts (0 on the bottom side), 41 nets.

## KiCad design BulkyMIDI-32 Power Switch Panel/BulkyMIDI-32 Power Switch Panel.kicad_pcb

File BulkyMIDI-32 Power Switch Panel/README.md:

# BulkyMIDI-32 Power Switch Panel
This is a front-facing panel for controlling the *BulkyMIDI-32 Power Switch*, while optional by design I find that it makes the system a lot more enjoyable in use and on my desk. The main PCB didn't have suffiecient room for the LEDs either, so if you'd like a little feedback on the currently active input channel then this is the panel for you.

- [1> Building the device](#1-building-the-device)
  - [1.1> Soldering it together](#11-soldering-it-together)
- [2> Schematic](#2-schematic)
- [3> BOM](#3-bom)

# 1> Building the device
Building a device such as this assumes you have at least minor experience soldering things together, recommended is that you at the very least have access to a soldering station with adjustable temperature. If currently available, you should probably start with 60/40 rosin core solder as the lead-free alternatives tends to be a bit harder to work with.

With requirements for basic equipment sorted, we need to talk a bit about what you want to achieve while building this project. The reason I ask is that while you can build a functional *power switch* using the main module by itself, you can also choose to build the complete version of it - this includes front panels and faceplates. 

Now that you know what you want to build, we can get started on the most expensive step in any build process - shopping! So, head on over to the [BOM](#3-bom)-section for some information on what kind of components that you'll need. While I would have liked to give you specific part numbers for "reputable" electronic part suppliers, I can't afford to shop there so I usually make due with what I can find on sites such as ebay, AliExpress and any similar sites that sell cheap chinese components. The downside to this is that I can't link to a part directly and expect it to stay listed, so you'll need to consider the description listed as suggested search terms.

## 1.1> Soldering it together

The construction of this unit should be fairly straight-forward, just take your time in order to make sure everything goes into place - more or less straight. I usually recommend starting by having a good look at the PCBs, try to figure out where all of the listed components go and in which orientation they go in (all of this should be clearly marked on the silkscreen). 

The first component to be added is the right-angle pin headers, these are soldered on the front side of the board instead of the component side. I've found that these are often somewhat warped, so I usually try to just solder the outer edges first, then reheat and adjust so that the plastic part sits completely flush against the board before tackling the remaining pins.

The next component to go on are the 8mm hex standoffs, they in particular need to be positioned so that a flat edge lines up with the lef and right edges of the PCB. As these are just nylon, I've made things slightly easier for myself by using a sharp knife to trim a bit off the vertical edges of them - in particular the one that sits just above the power LED.

Here I've simply inserted the LEDs into the footprints (longer pin goes into the round pad), the same goes for the six switches before adding the front panel to the front of it.  Continuing on with the LEDs I'll tack one of the pins into place, then while reheating the pin I'll try and push slightly on it to ensure that it is perfectly aligned with the holes on the front panel before soldering the remaining pin. The switches mostly stick to their expected alignment, but feel free to use the same method except that you push from the from.

The front panel have been removed again, mostly because it'll slightly be in the way when installing it onto the main [Audio Switch](https://github.com/tebl/BulkyMIDI-32/tree/main/BulkyMIDI-32%20Audio%20Switch) PCB. If you're a perfectionist like me, you may want to deal with some of the light bleed that you'll inevitably get between the LEDs.

The easiest solution for this came to me in the middle of a dark and stormy night, standard heat shrink tubing with a diameter of at least 5mm. Using an 8mm hex standoff as a guide and a sharp knife, I cut it up into 8mm segments that was then just put on top of the LEDs. If you have a hot air station you can shrink it a bit to keep it from falling off when the front panel is removed, but as long as it stays in place they should as well. 

# 2> Schematic
The supplied KiCad files should be sufficient as both a schematic and as a  starting point for ordering PCBs (basically you could just zip the contents of the export folder and upload that on a fabrication site), the schematic is also available in [PDF-format](https://github.com/tebl/BulkyMIDI-32/tree/main/documentation/schematic) and this is what you'll need to print and work your way through this things don't work as expected after assembly.

# 3> BOM
Most parts should be easy to get a hold of from your favourite local electronic component shop, but given that I don't have access to such shops where I live so everything was based on whatever I could get cheapest from eBay/AliExpress (free shipping, but plan on waiting 3-4 weeks for delivery). Components in parenthesis can be considered optional for features beyond the more basic functionality, but where's the fun in that? You deserve the complete package.

| Reference             | Item                                                              | Count | Order  |
| --------------------- | ----------------------------------------------------------------- | ----- | ------ |
| Panel PCB             | Fabricate using Gerber files                                      |     1 | PCBWay
| D1-D6                 | 5mm LEDs, preferably frosted (not the bright clear ones)          |     6 |
| J1                    | Breakable right-angle pin header                                  |     1 |
| SW1-SW6               | 6x6x11mm momentary button                                         |     6 |
| Mounting ****         | Nylon M3 hex standoffs 8mm (M-F)                                  |     4 |
| Mounting ****         | Nylon M3x6mm nylon screws                                         |     4 |
| Mounting ****         | Nylon M3x6mm nylon nuts                                           |     4 |

****) These are available in the form of kits usually advertised *M3 nylon standoff kit* which should contain most of what you'd need. I do however recommend that you pick up extra M-F standoffs of lengths 8mm and 20mm, as quite a lot of them will be used when building more than one module.

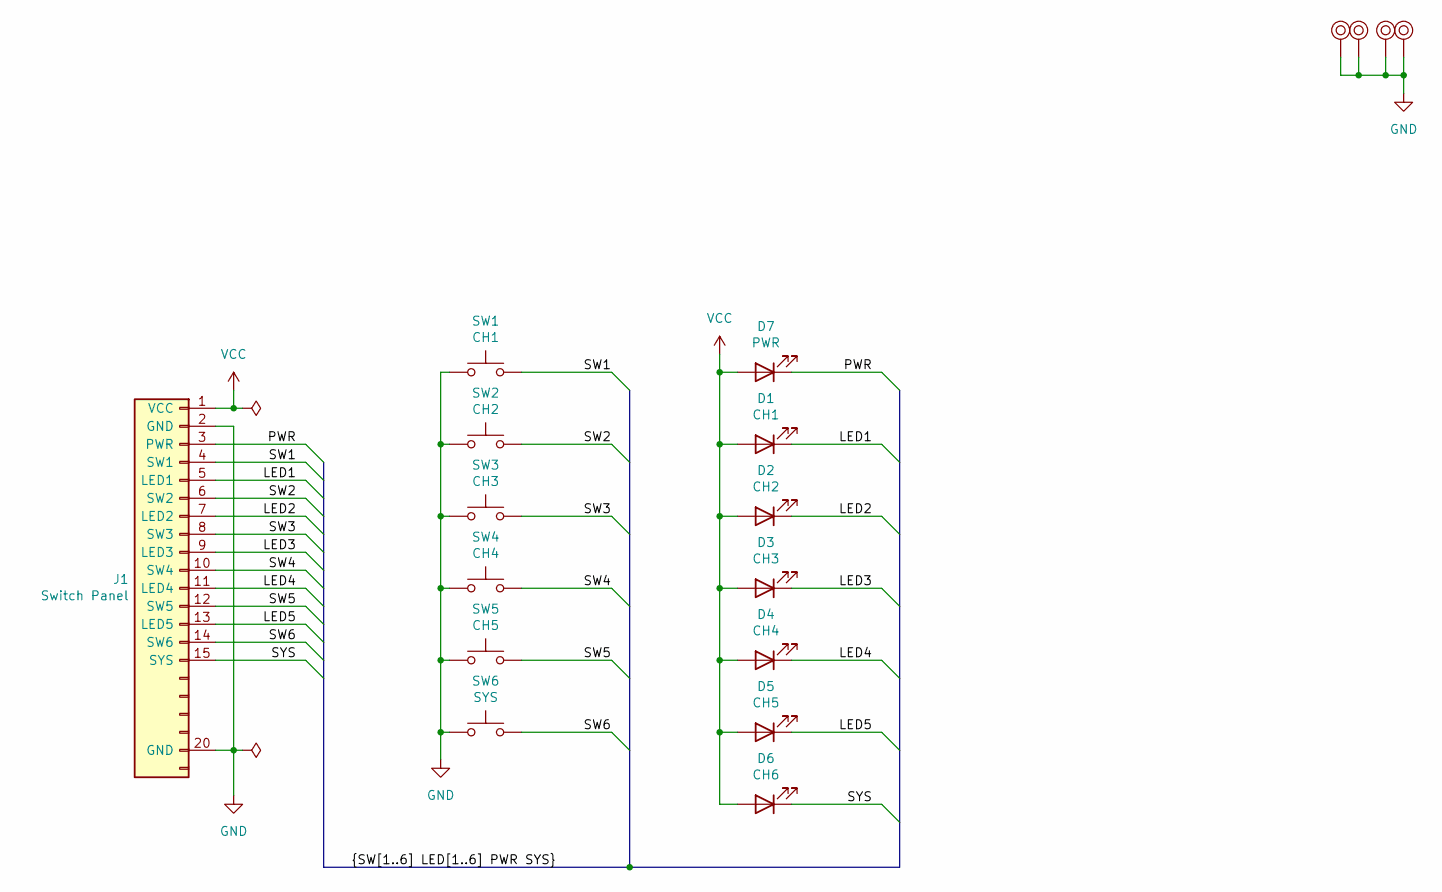
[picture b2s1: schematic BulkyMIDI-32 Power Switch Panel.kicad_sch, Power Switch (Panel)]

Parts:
D1: CH1; LED_D5.0mm
D2: CH2; LED_D5.0mm
D3: CH3; LED_D5.0mm
D4: CH4; LED_D5.0mm
D5: CH5; LED_D5.0mm
D6: CH6; LED_D5.0mm
D7: PWR; LED_D5.0mm
J1: Switch Panel; PinHeader_1x21_P2.54mm_Horizontal
M1, M2, M3, M4: Mounting_Pin; M3_pin
SW1: CH1; SW_PUSH_6mm
SW2: CH2; SW_PUSH_6mm
SW3: CH3; SW_PUSH_6mm
SW4: CH4; SW_PUSH_6mm
SW5: CH5; SW_PUSH_6mm
SW6: SYS; SW_PUSH_6mm

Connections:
/LED1: D1.1 (K), J1.5 (LED1)
/LED2: D2.1 (K), J1.7 (LED2)
/LED3: D3.1 (K), J1.9 (LED3)
/LED4: D4.1 (K), J1.11 (LED4)
/LED5: D5.1 (K), J1.13 (LED5)
/PWR: D7.1 (K), J1.3 (PWR)
/SW1: J1.4 (SW1), SW1.2
/SW2: J1.6 (SW2), SW2.2
/SW3: J1.8 (SW3), SW3.2
/SW4: J1.10 (SW4), SW4.2
/SW5: J1.12 (SW5), SW5.2
/SW6: J1.14 (SW6), SW6.2
/SYS: D6.1 (K), J1.15 (SYS)
GND: J1.2 (GND), J1.20 (GND), M1.1, M2.1, M3.1, M4.1, SW1.1, SW2.1, SW3.1, SW4.1, SW5.1, SW6.1
VCC: D1.2 (A), D2.2 (A), D3.2 (A), D4.2 (A), D5.2 (A), D6.2 (A), D7.2 (A), J1.1 (VCC)

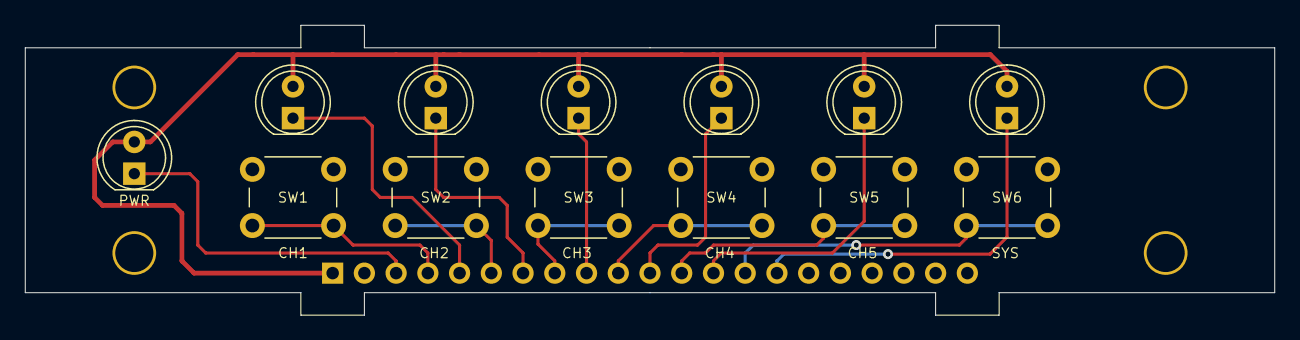
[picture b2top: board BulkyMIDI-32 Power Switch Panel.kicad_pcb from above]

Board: 2 copper layers, 100.0 x 23.2 mm, 18 parts (1 on the bottom side), 15 nets.
